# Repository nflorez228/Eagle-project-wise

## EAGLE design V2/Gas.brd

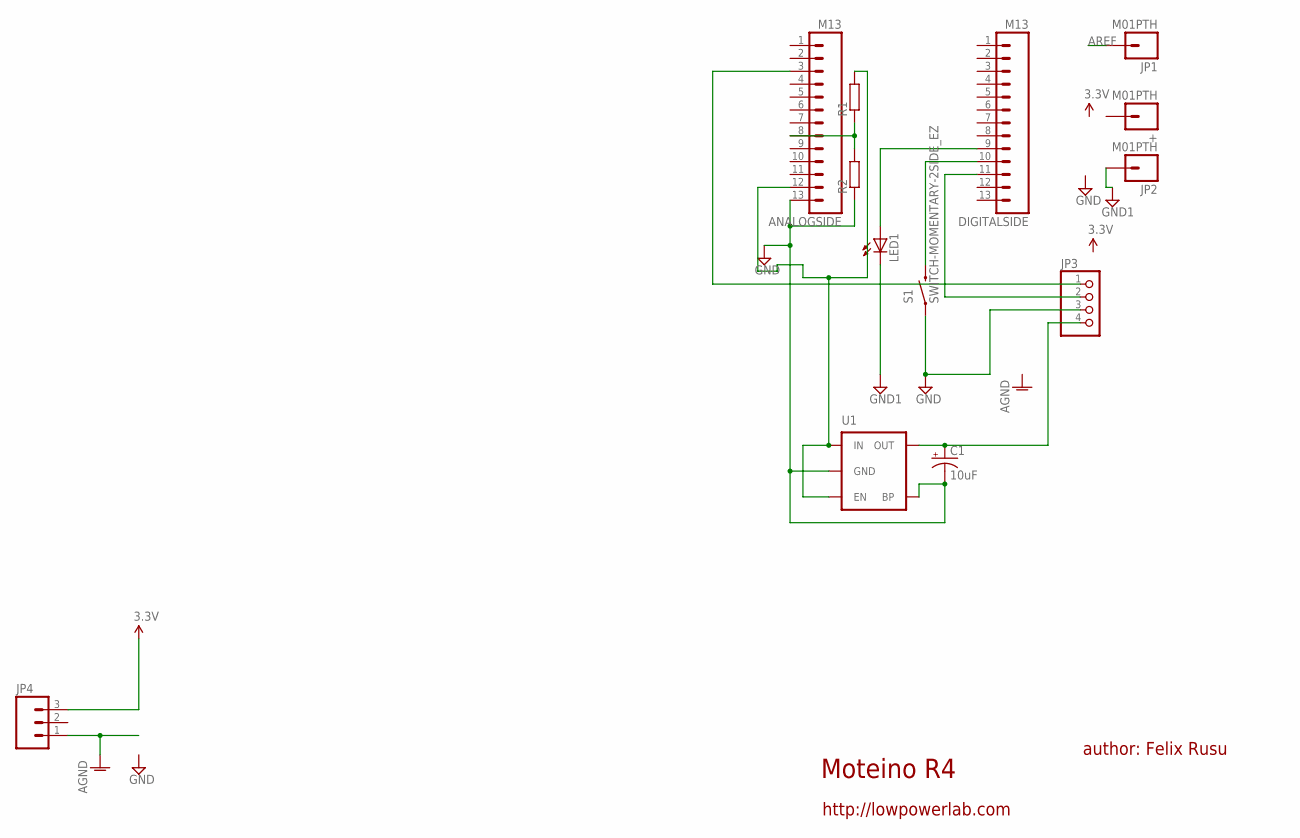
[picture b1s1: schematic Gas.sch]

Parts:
+: M01PTH; 1X01
ANALOGSIDE: M13; 1X13
C1: 10uF; EIA3216
DIGITALSIDE: M13; 1X13
JP1, JP2: M01PTH; 1X01
JP3: PINHD-1X4; 1X04
JP4: M03PTH; 1X03
LED1: LED3MM
R1, R2: R-EU_0204/7; 0204/7
S1: SWITCH-MOMENTARY-2SIDE_EZ; TACTILE-PTH-SIDEEZ
U1: MIC52055V; SOT23-5

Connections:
AGND: JP4.1
AREF: JP1.1
GND: ANALOGSIDE.13, C1.C (-), JP3.3, R2.1, S1.1, U1.2 (GND), U1.4 (BP)
GND1: JP2.1, LED1.K (C)
unnamed: DIGITALSIDE.10, S1.2
unnamed: DIGITALSIDE.11, JP3.2
unnamed: ANALOGSIDE.3, JP3.1
unnamed: ANALOGSIDE.12, R1.2, U1.1 (IN), U1.3 (EN)
unnamed: ANALOGSIDE.8, R1.1, R2.2
unnamed: DIGITALSIDE.9, LED1.A
unnamed: C1.A (+), JP3.4, U1.5 (OUT)
VCC: JP4.3

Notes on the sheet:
Moteino R4
author: Felix Rusu
http://lowpowerlab.com

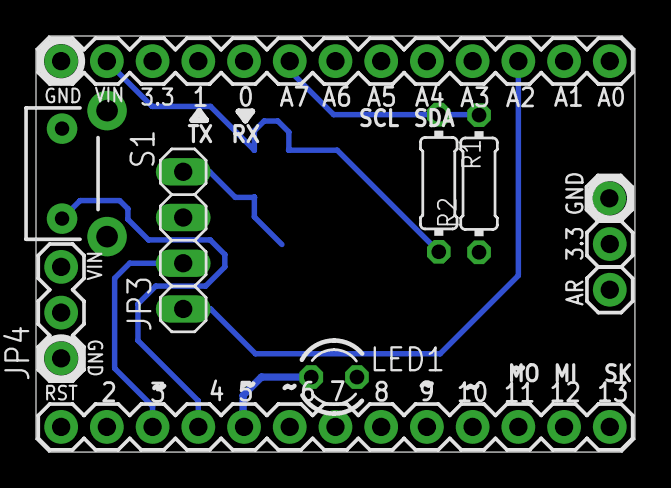
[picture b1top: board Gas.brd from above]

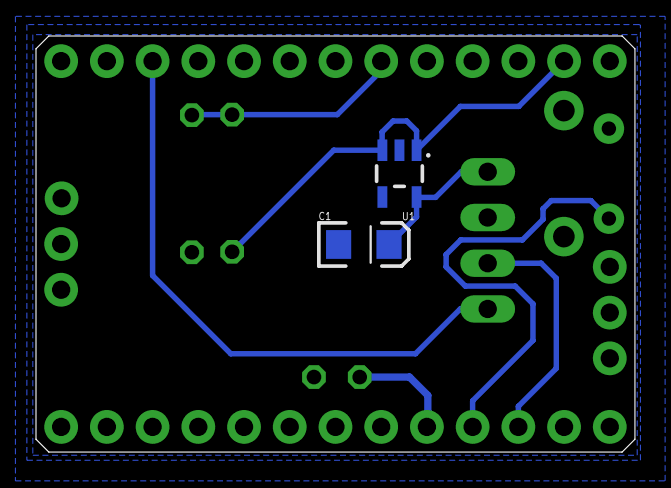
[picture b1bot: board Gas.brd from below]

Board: 2 copper layers, 33.3 x 23.1 mm, 13 parts (2 on the bottom side), 9 nets.

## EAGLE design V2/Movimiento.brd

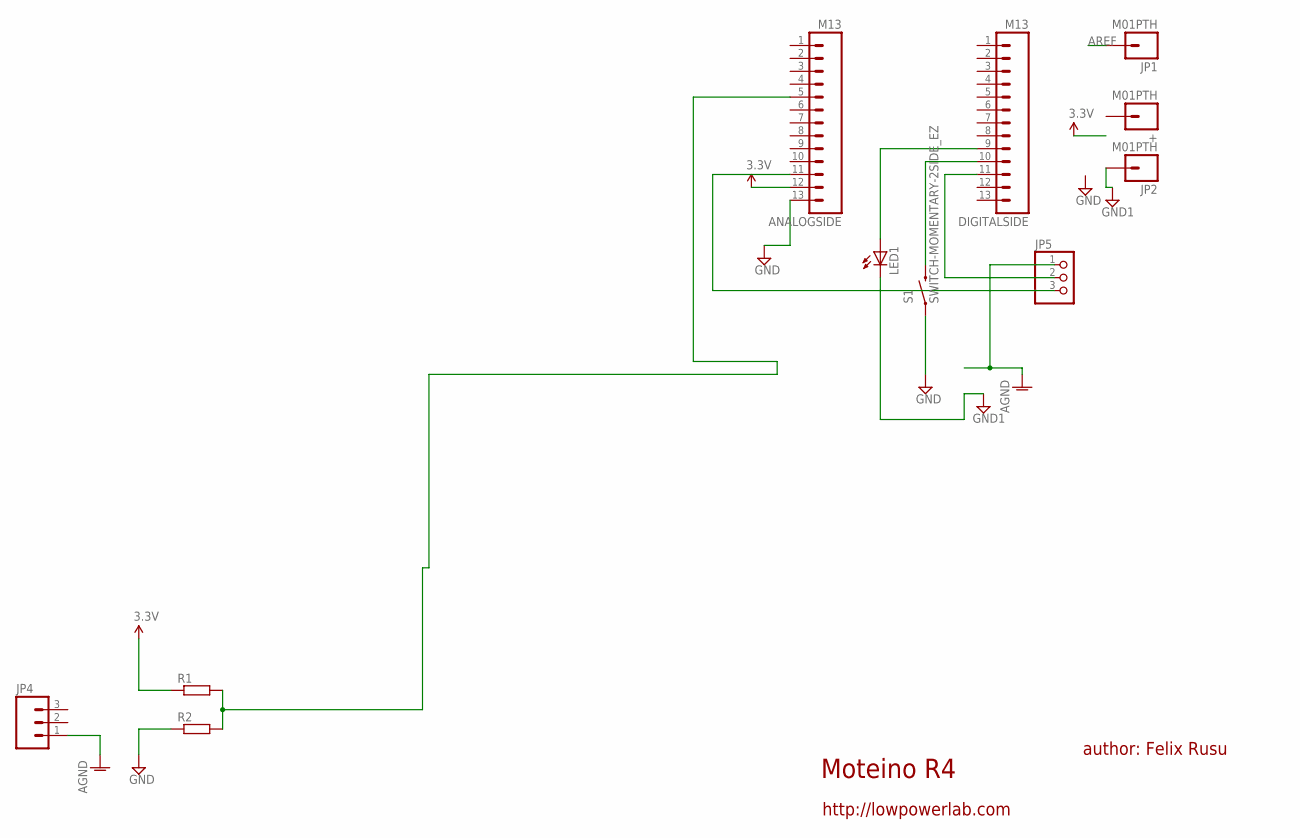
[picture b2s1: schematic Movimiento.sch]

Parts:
+: M01PTH; 1X01
ANALOGSIDE: M13; 1X13
DIGITALSIDE: M13; 1X13
JP1, JP2: M01PTH; 1X01
JP4: M03PTH; 1X03
JP5: PINHD-1X3; 1X03
LED1: LED3MM
R1, R2: R-EU_0204/7; 0204/7
S1: SWITCH-MOMENTARY-2SIDE_EZ; TACTILE-PTH-SIDEEZ

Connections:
AGND: JP4.1, JP5.1
AREF: JP1.1
GND: ANALOGSIDE.13, R2.1, S1.1
GND1: JP2.1, LED1.K (C)
unnamed: DIGITALSIDE.10, S1.2
unnamed: DIGITALSIDE.11, JP5.2
unnamed: ANALOGSIDE.11, JP5.3
unnamed: DIGITALSIDE.9, LED1.A
unnamed: ANALOGSIDE.5, R1.2, R2.2
VCC: ANALOGSIDE.12, R1.1

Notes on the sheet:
Moteino R4
author: Felix Rusu
http://lowpowerlab.com

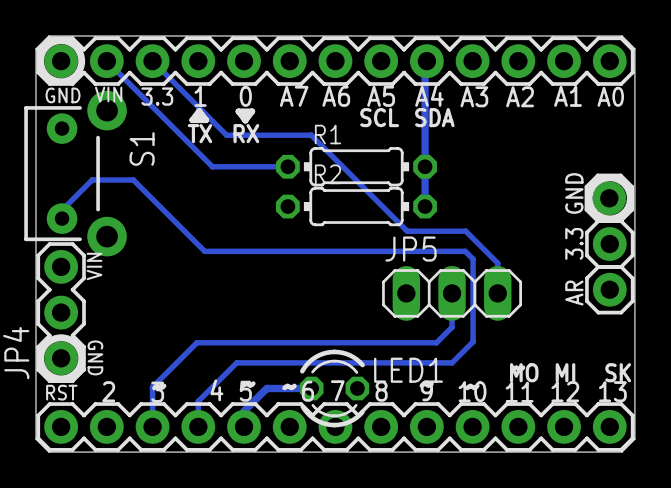
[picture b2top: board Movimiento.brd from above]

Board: 2 copper layers, 33.3 x 23.1 mm, 11 parts (0 on the bottom side), 9 nets.

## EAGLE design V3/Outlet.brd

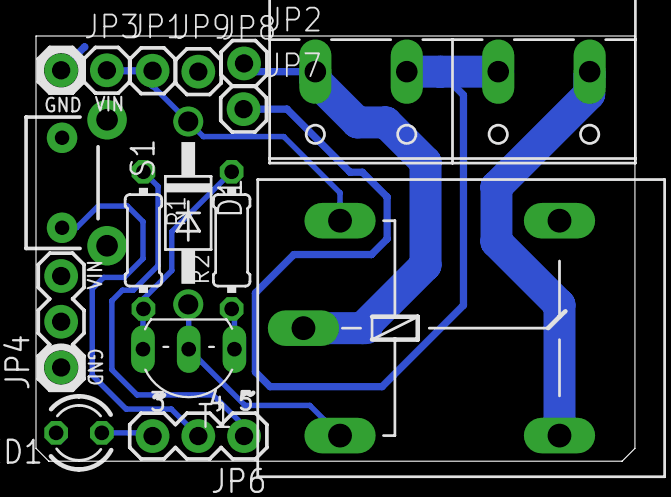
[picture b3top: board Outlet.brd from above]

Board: 2 copper layers, 33.3 x 23.6 mm, 16 parts (0 on the bottom side), 11 nets.

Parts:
D1: 1N4004; DO41-10
JP1, JP2, JP3, JP7, JP8, JP9: M01PTH; 1X01
JP4, JP6: 1X03
K1: G5L; G5LE
LED1: LED3MM
R1, R2: 0204/7
S1: SWITCH-MOMENTARY-2SIDE_EZ; TACTILE-PTH-SIDEEZ
T1: 2SC458; TO92-ECB
X1: Out- In- Out+ In+; W237-4P

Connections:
AGND: JP4.1, LED1.K
GND: JP3.1, JP8.1, R2.1, S1.1, T1.E
unnamed: JP6.2, S1.2
unnamed: JP7.1, X1.2, X1.3
unnamed: JP6.3, LED1.A
unnamed: R1.2, R2.2, T1.B
unnamed: D1.A, K1.1, T1.C
unnamed: D1.C, JP1.1, JP9.1, K1.2
unnamed: K1.S, X1.1
unnamed: JP2.1, K1.P, X1.4
unnamed: JP6.1, R1.1

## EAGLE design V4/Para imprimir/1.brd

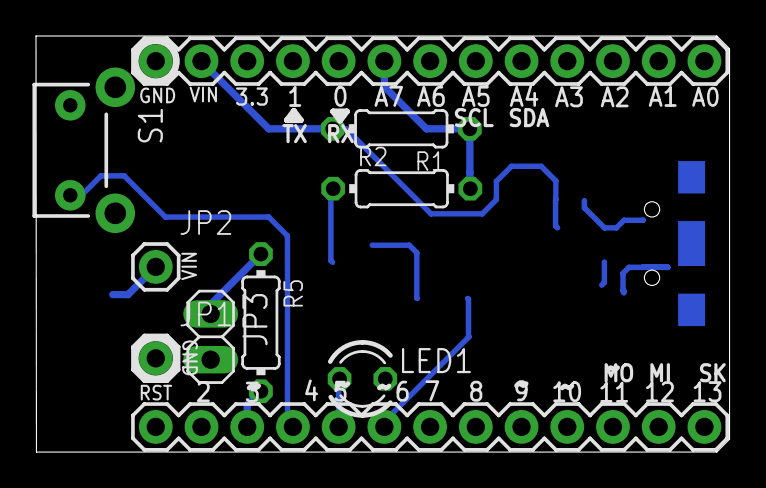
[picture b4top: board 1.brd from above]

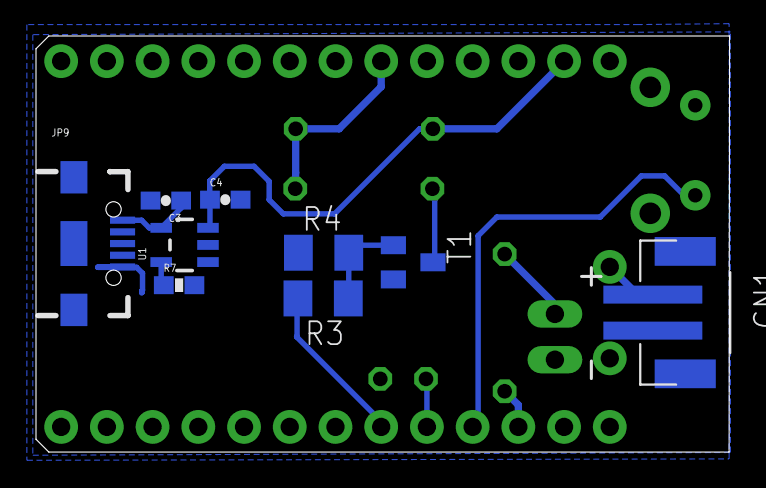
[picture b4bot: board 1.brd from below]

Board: 2 copper layers, 38.5 x 23.1 mm, 19 parts (9 on the bottom side), 14 nets.

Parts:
ANALOGSIDE: M13; 1X13
C3, C4: 4.7uF; 0603-CAP
CN1: JST-PH-2-SMT
DIGITALSIDE: M13; 1X13
JP1, JP2: M01PTH; 1X01
JP3: 1X02
JP9: Micro USB; USB-AB-MICRO-SMD_V03
LED1: LED3MM
R1, R2, R5: 0204/7
R3, R4: M1206
R7: 2.0k; 0603-RES
S1: SWITCH-MOMENTARY-2SIDE_EZ; TACTILE-PTH-SIDEEZ
T1: BC850; SOT23
U1: MCP73831; SOT23-5

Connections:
AGND: CN1.2, JP1.1, JP3.2
GND: ANALOGSIDE.13, C3.2, C4.2, JP9.GND1, LED1.K, R4.1, R7.2, S1.1, T1.2, U1.2
unnamed: DIGITALSIDE.10, S1.2
unnamed: JP3.1, R5.1
unnamed: DIGITALSIDE.9, LED1.A
unnamed: C3.1, JP9.VBUS1, U1.4
unnamed: ANALOGSIDE.8, R1.1, R2.2
unnamed: R2.1, T1.3
unnamed: R3.1, R4.2, T1.1
unnamed: DIGITALSIDE.8, R3.2
unnamed: DIGITALSIDE.11, R5.2
PROG: R7.1, U1.5
VCC: CN1.1, JP2.1
VIN: ANALOGSIDE.12, C4.1, R1.2, U1.3

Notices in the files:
parts and their libraries:
SparkFun-Connectors: Licensing: CC v3.0 Share-Alike You are welcome to use this library for commercial purposes.
SparkFun-Electromechanical: Licensing: Creative Commons ShareAlike 4.0 International - https://creativecommons.org/licenses/by-sa/4.0
